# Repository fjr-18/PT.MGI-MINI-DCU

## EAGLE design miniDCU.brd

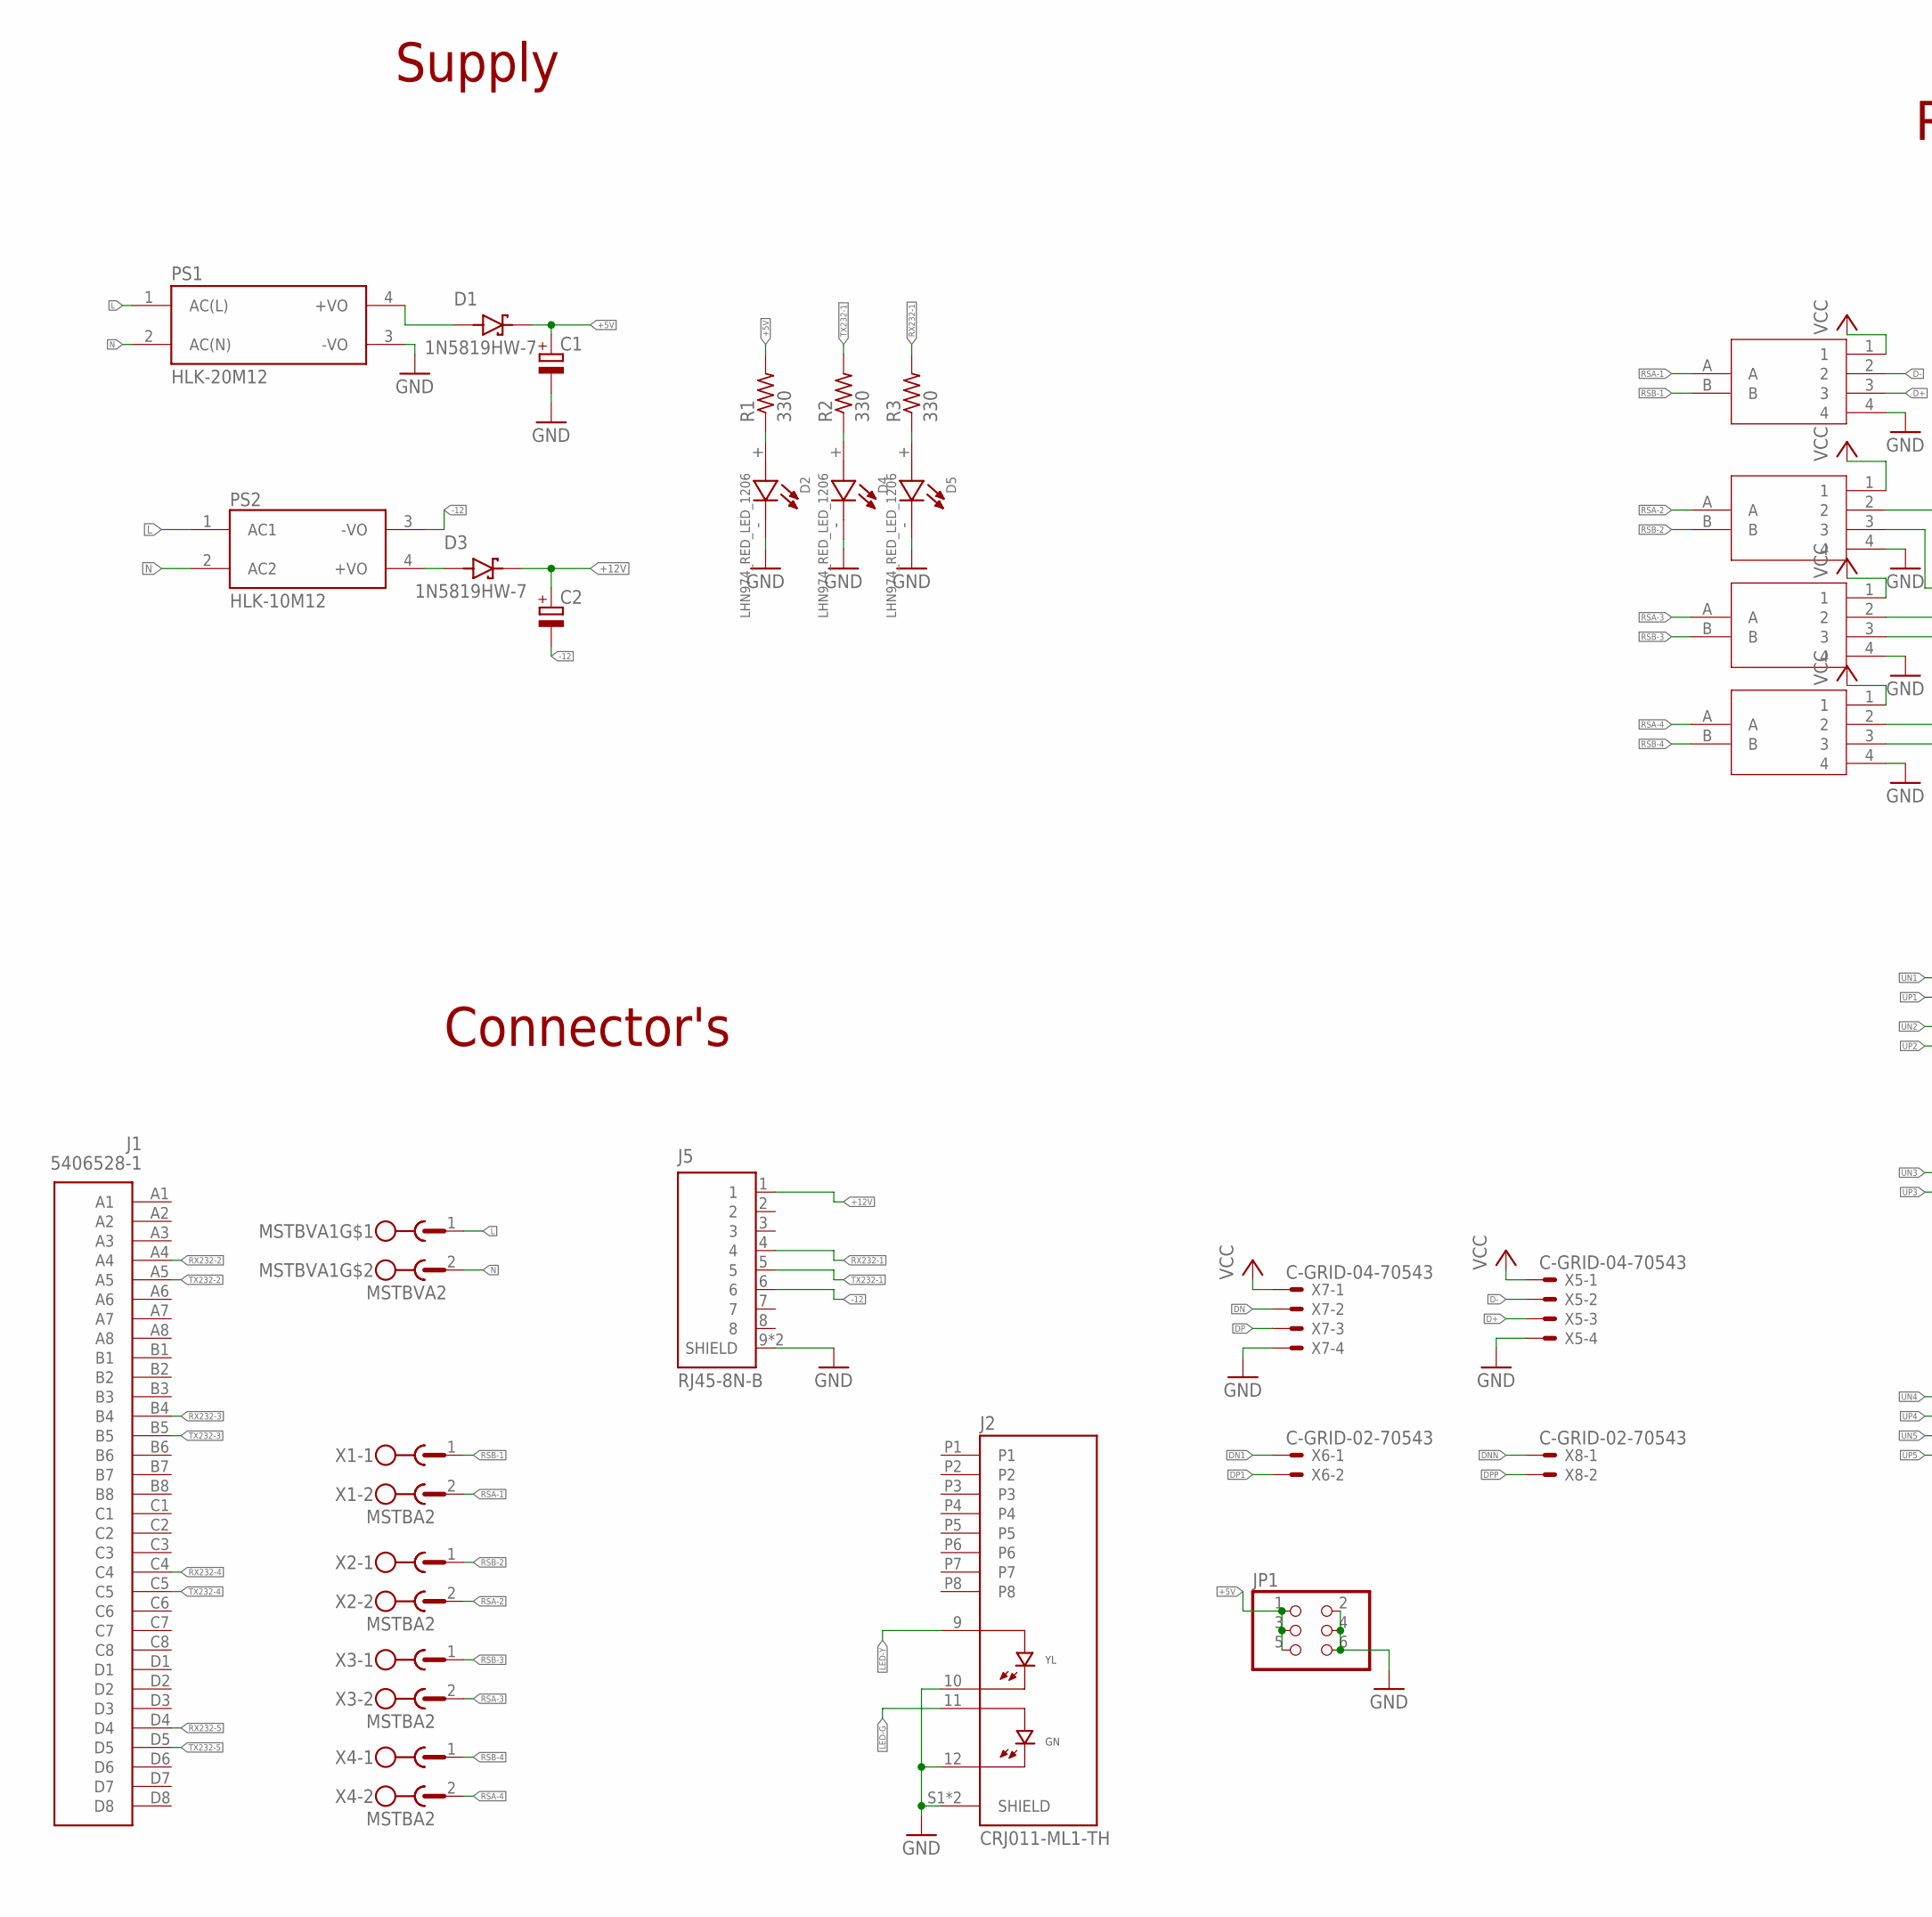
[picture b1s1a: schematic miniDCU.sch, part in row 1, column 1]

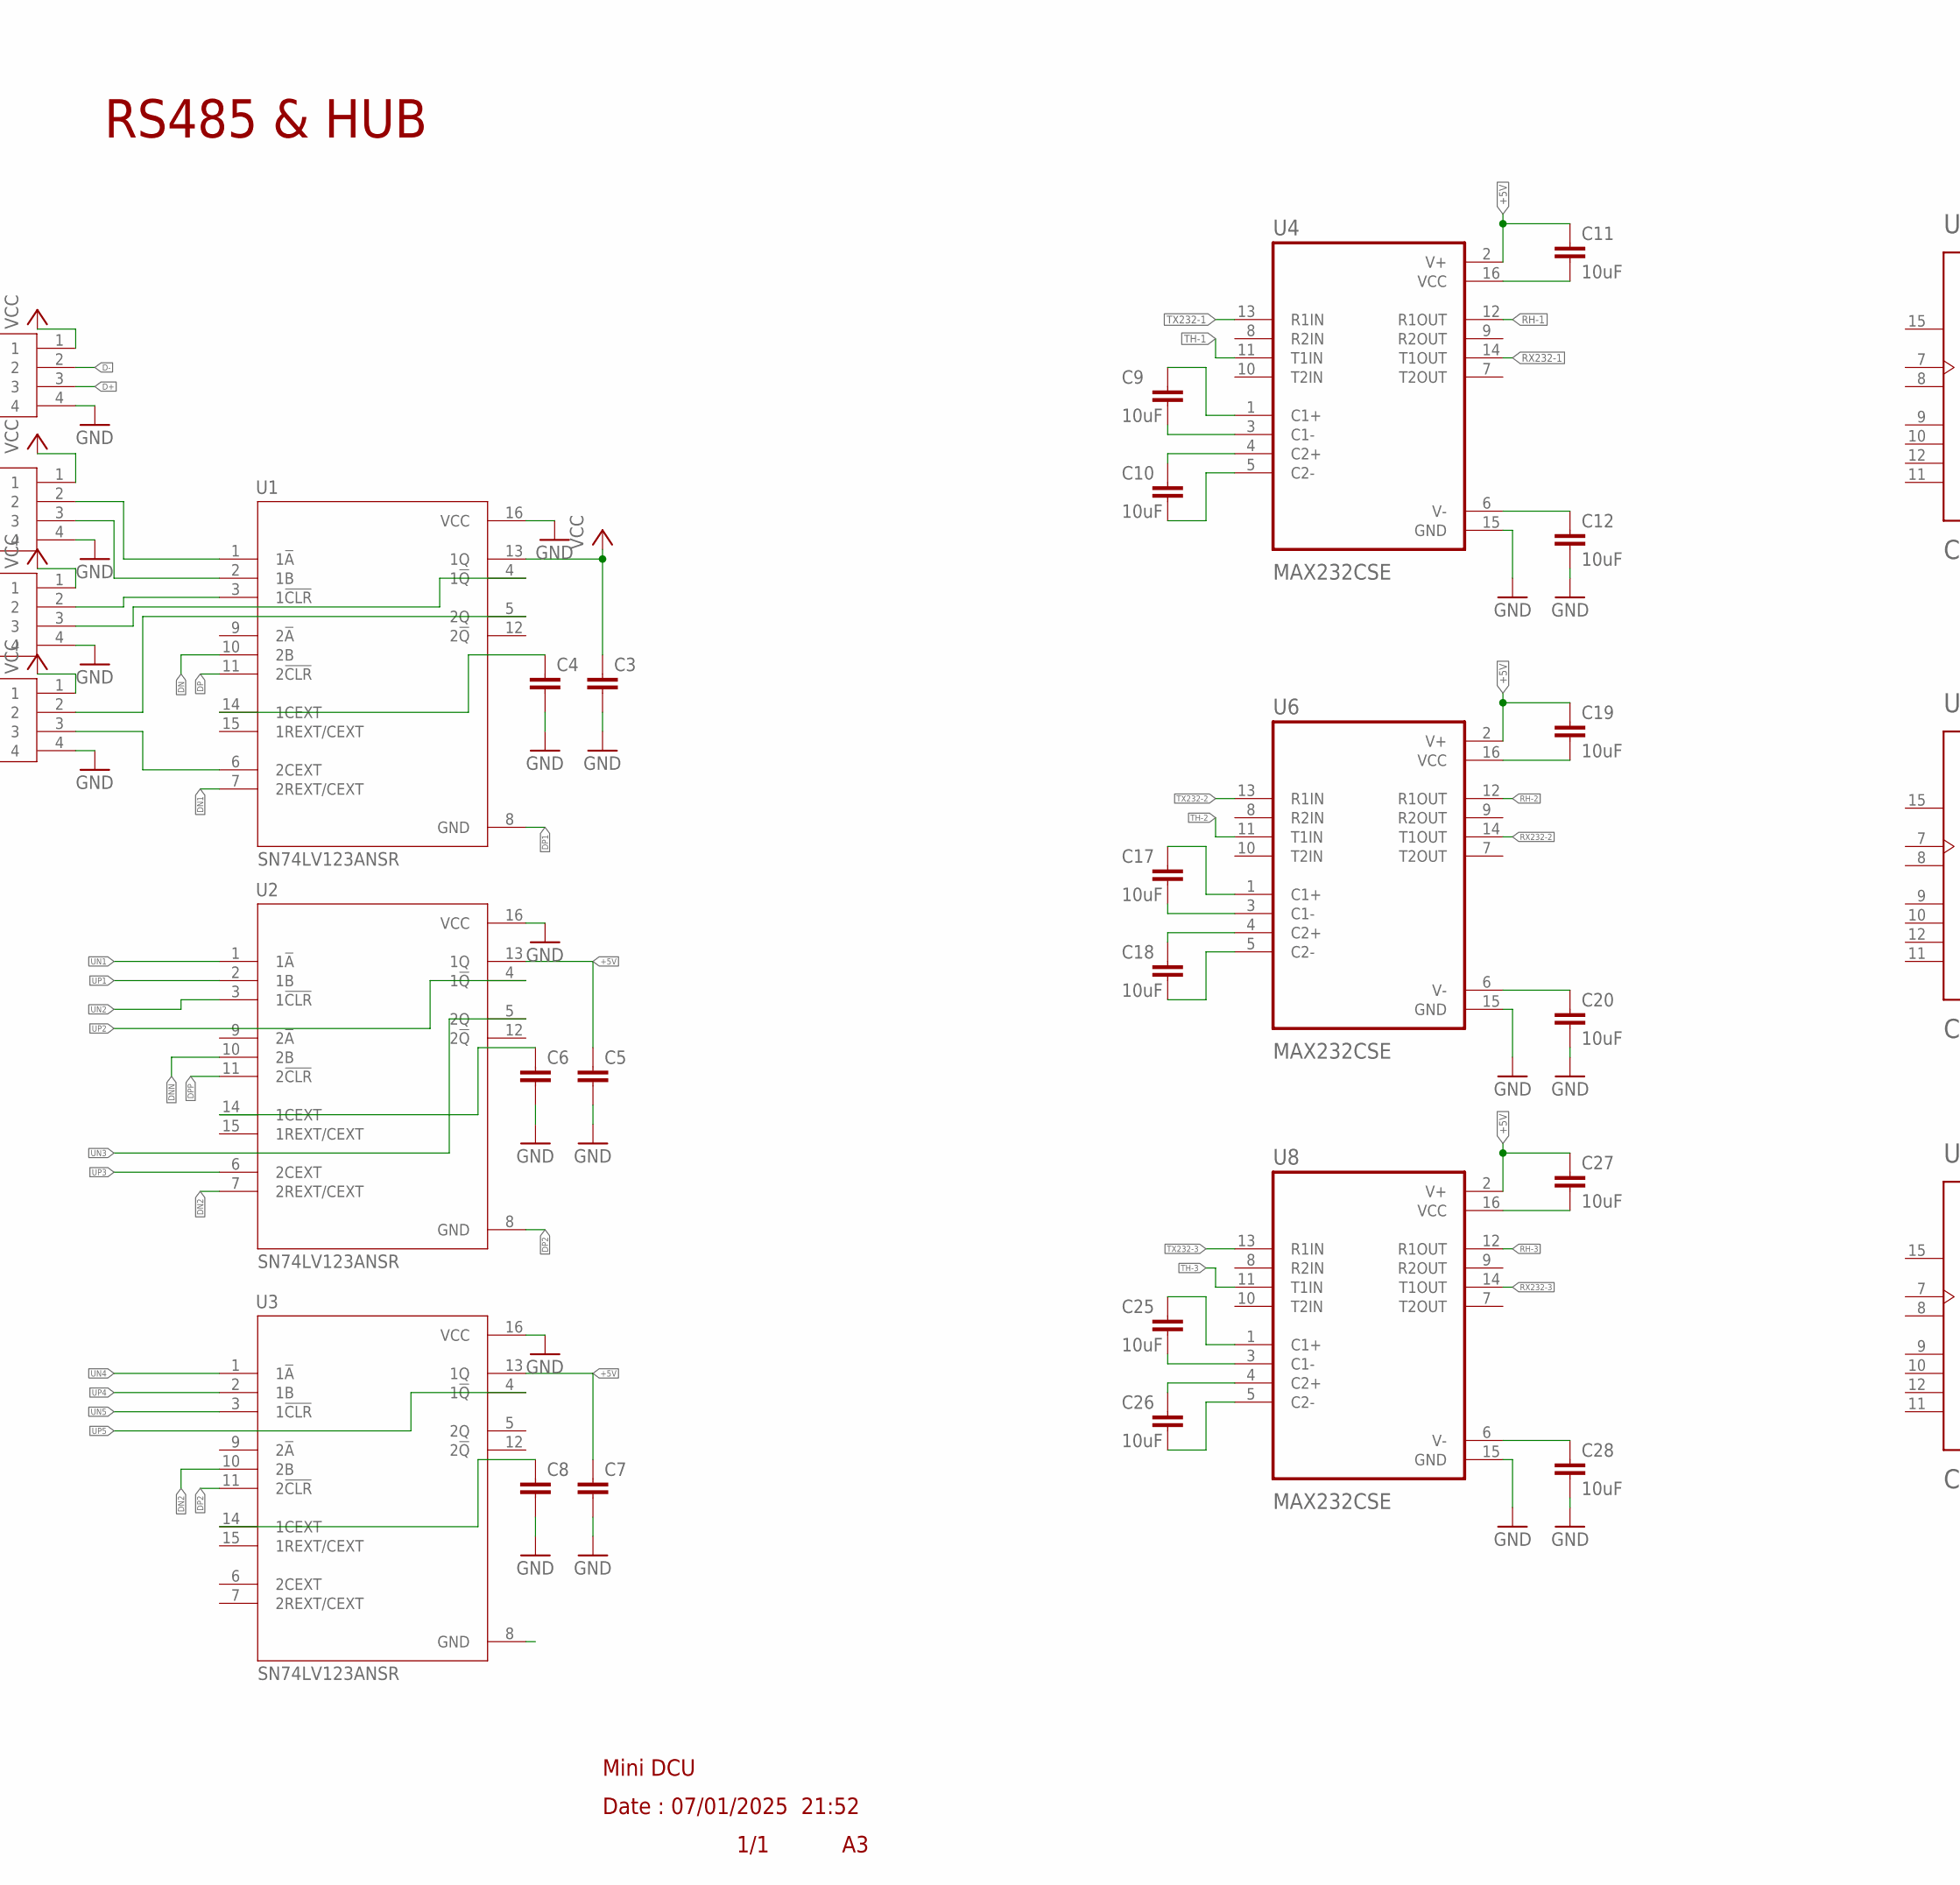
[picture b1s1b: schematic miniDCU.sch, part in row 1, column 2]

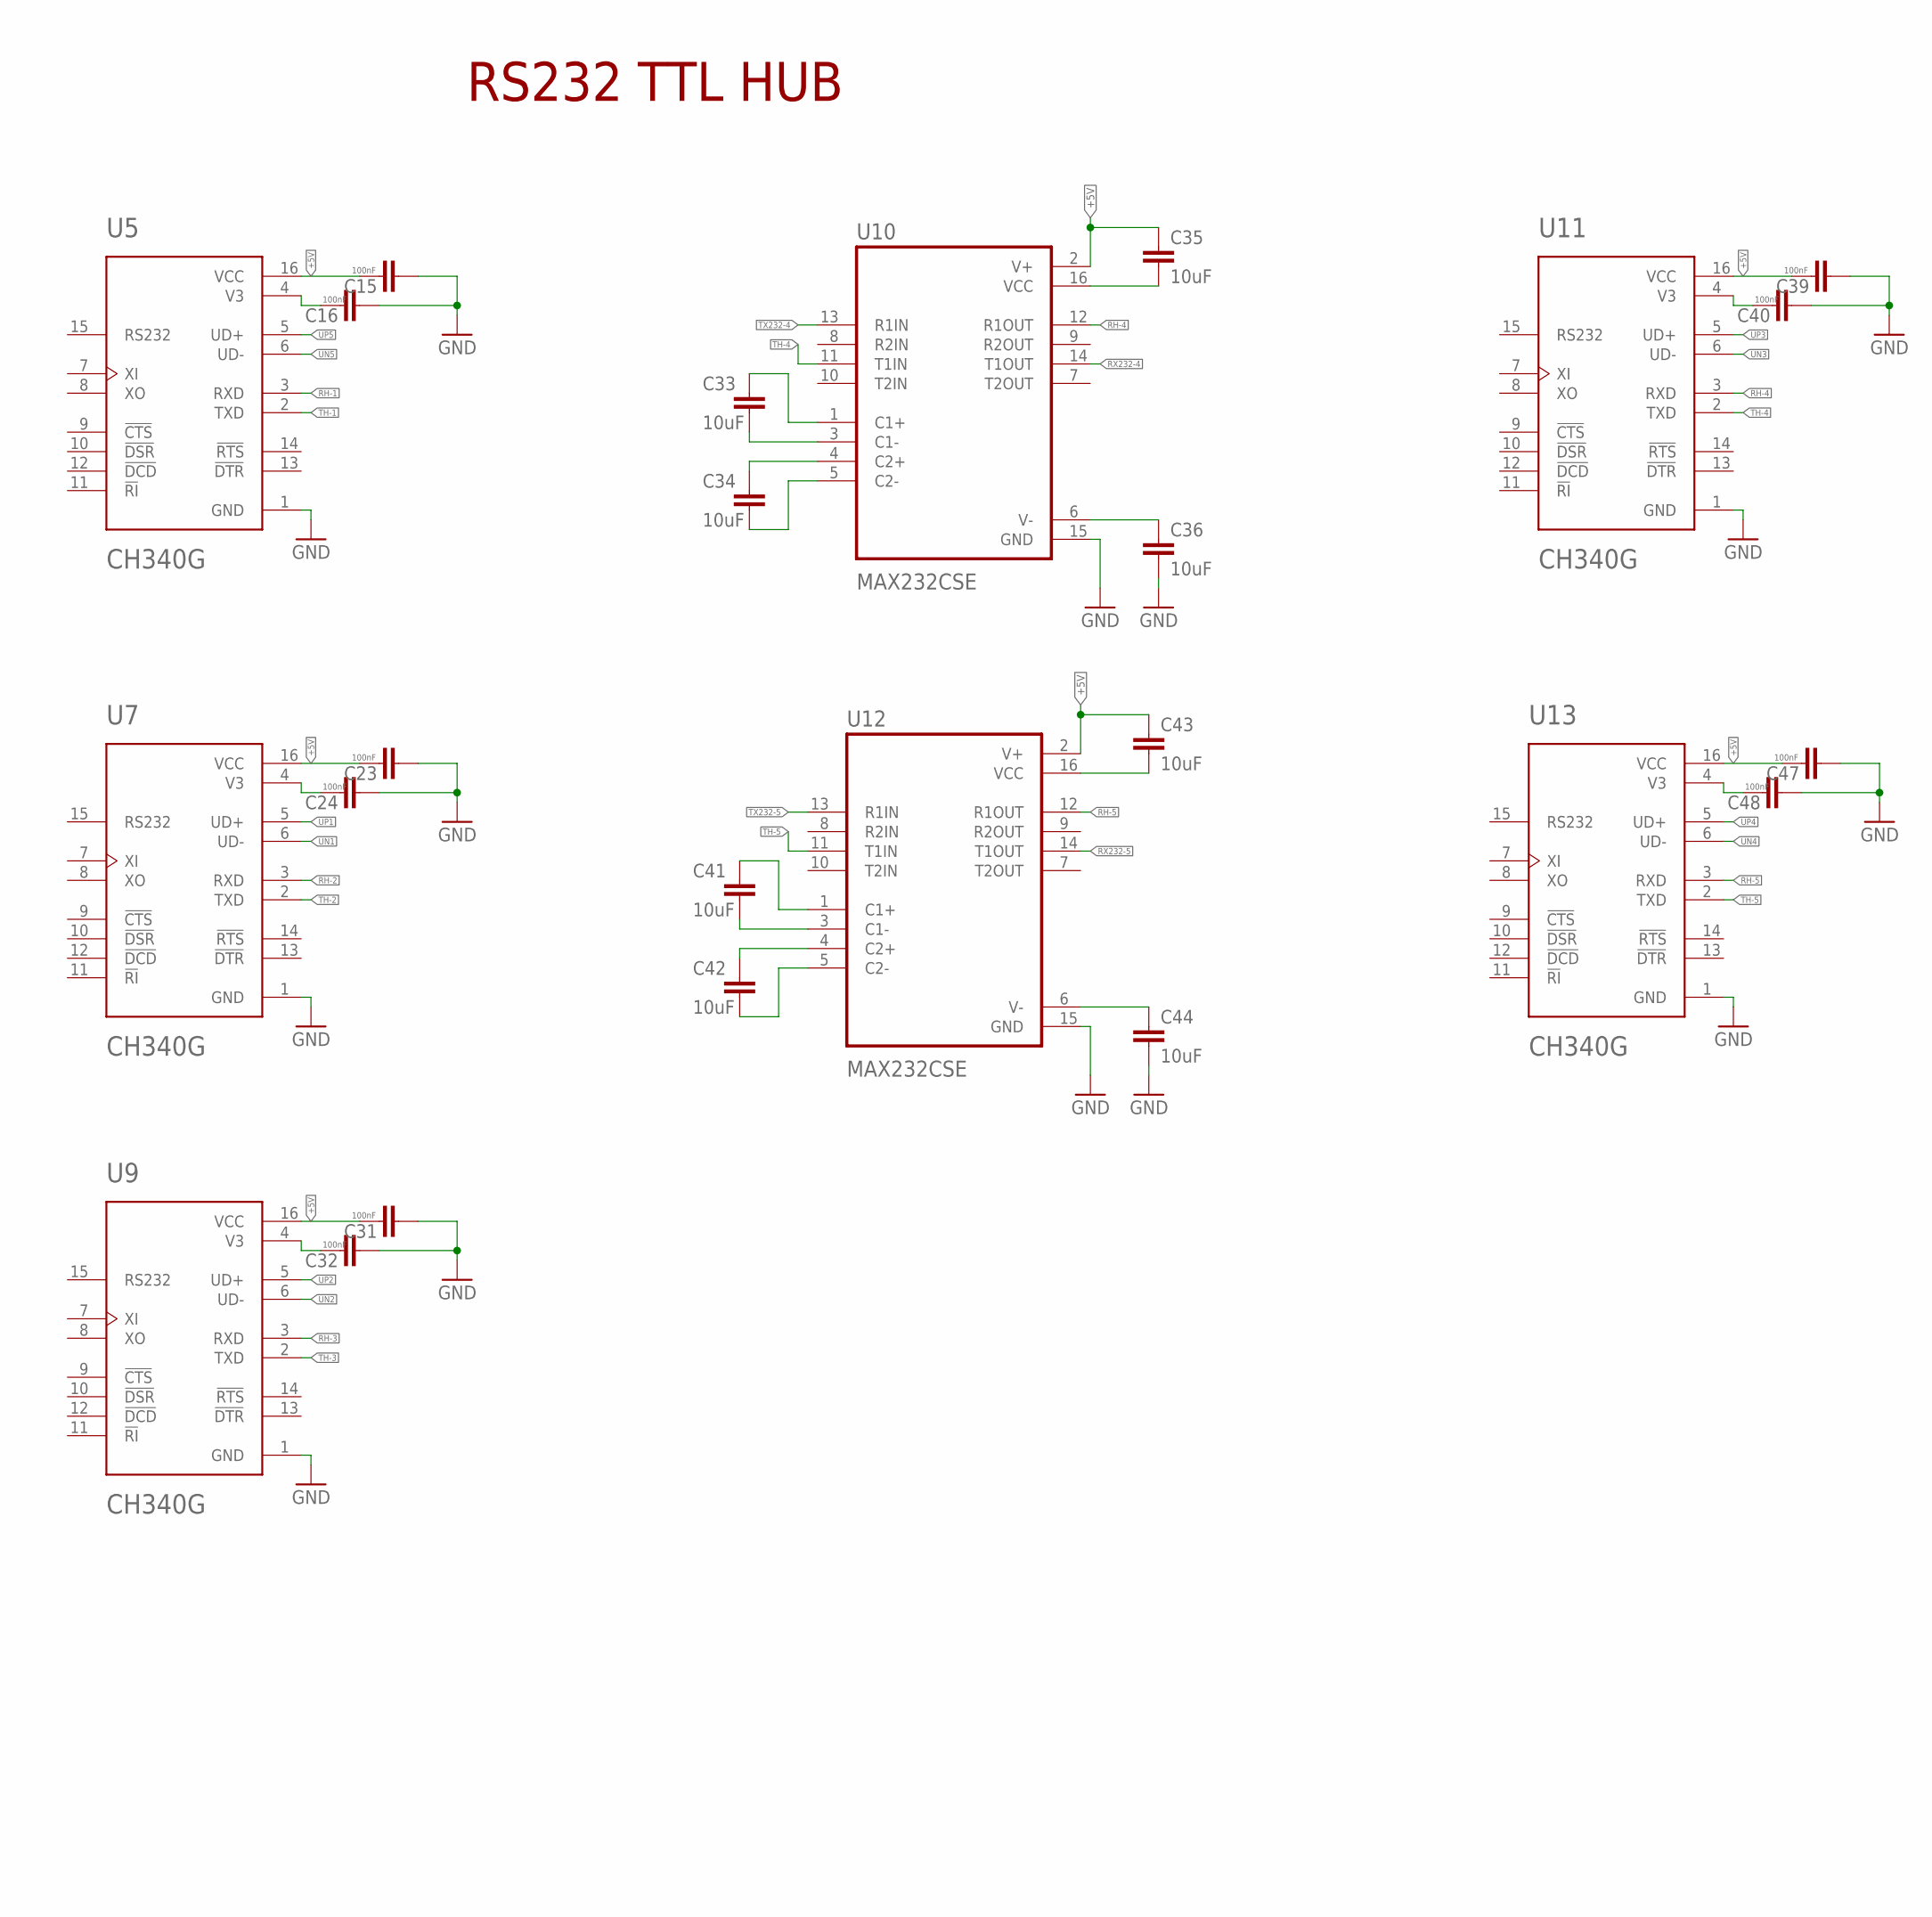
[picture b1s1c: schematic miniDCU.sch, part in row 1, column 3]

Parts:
C1, C2: CPOL-EU153CLV-0505; 153CLV-0505
C3, C4, C5, C6, C7, C8: C-EUC0603K; C0603K
C9, C10, C11, C12, C17, C18, C19, C20, C25, C26, C27, C28, C33, C34, C35, C36, C41, C42, C43, C44: 10uF; C0805
C15, C16, C23, C24, C31, C32, C39, C40, C47, C48: 100nF; C0805K
D1, D3: 1N5819HW-7; SOD3715X145N
D2, D4, D5: LHN974_RED_LED_1206; LEDC3216X120N
J1: 5406528-1
J2: CRJ011-ML1-TH; CUI_CRJ011-ML1-TH
J5: RJ45-8N-B; TE_RJ45-8N-B
JP1: PINHD-2X3; 2X03
MSTBVA1: MSTBVA2
PS1: HLK-20M12; CONV_HLK-20M12
PS2: HLK-10M12; CONV_HLK-10M12
R1, R2, R3: 330; M0805
U1, U2, U3: SN74LV123ANSR; SOIC127P780X200-16N
U4, U6, U8, U10, U12: MAX232CSE; SOIC127P600X175-16N
U5, U7, U9, U11, U13: CH340G; SOIC127P600X180-16N
USB2RS1, USB2RS2, USB2RS3, USB2RS5: USB2RS485
X1, X2, X3, X4: MSTBA2
X5, X7: C-GRID-04-70543; 70543-04
X6, X8: C-GRID-02-70543; 70543-02

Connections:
+5V: C1.+, C5.1, C7.1, C11.1, C15.1, C19.1, C23.1, C27.1, C31.1, C35.1, C39.1, C43.1, C47.1, D1.C (K), JP1.1, JP1.3, JP1.5, R1.2, U2.13 (1Q), U3.13 (1Q), U4.2 (V+), U5.16 (VCC), U6.2 (V+), U7.16 (VCC), U8.2 (V+), U9.16 (VCC), U10.2 (V+), U11.16 (VCC), U12.2 (V+), U13.16 (VCC)
+12V: C2.+, D3.C (K), J5.1
-12: C2.-, J5.6, PS2.3 (-VO)
D+: USB2RS5.3, X5.3
D-: USB2RS5.2, X5.2
DN: U1.10 (2B), X7.2
DN1: U1.7 (2REXT/CEXT), X6.1
DN2: U2.7 (2REXT/CEXT), U3.10 (2B)
DNN: U2.10 (2B), X8.1
DP: U1.11 (2!CLR), X7.3
DP1: U1.8 (GND), X6.2
DP2: U2.8 (GND), U3.11 (2!CLR)
DPP: U2.11 (2!CLR), X8.2
GND: C1.-, C3.2, C4.2, C5.2, C6.2, C7.2, C8.2, C12.2, C15.2, C16.2, C20.2, C23.2, C24.2, C28.2, C31.2, C32.2, C36.2, C39.2, C40.2, C44.2, C47.2, C48.2, D2.-, D4.-, D5.-, J2.10, J2.12, J2.S1 (SHIELD), J2.S2 (SHIELD), J5.9 (SHIELD), J5.10 (SHIELD), JP1.2, JP1.4, JP1.6, PS1.3 (-VO), U1.16 (VCC), U2.16 (VCC), U3.16 (VCC), U4.15 (GND), U5.1 (GND), U6.15 (GND), U7.1 (GND), U8.15 (GND), U9.1 (GND), U10.15 (GND), U11.1 (GND), U12.15 (GND), U13.1 (GND), USB2RS1.4, USB2RS2.4, USB2RS3.4, USB2RS5.4, X5.4, X7.4
L: MSTBVA1.1, PS1.1 (AC(L)), PS2.1 (AC1)
LED-G: J2.11
LED-Y: J2.9
N: MSTBVA1.2, PS1.2 (AC(N)), PS2.2 (AC2)
unnamed: D1.A, PS1.4 (+VO)
unnamed: D4.+, R2.1
unnamed: D2.+, R1.1
unnamed: D5.+, R3.1
unnamed: D3.A, PS2.4 (+VO)
unnamed: C9.2, U4.3 (C1-)
unnamed: C9.1, U4.1 (C1+)
unnamed: C10.1, U4.4 (C2+)
unnamed: C10.2, U4.5 (C2-)
unnamed: C11.2, U4.16 (VCC)
unnamed: C12.1, U4.6 (V-)
unnamed: U1.1 (1!A), USB2RS1.2
unnamed: U1.2 (1B), USB2RS1.3
unnamed: U1.3 (1!CLR), USB2RS2.2
unnamed: U1.4 (1!Q), USB2RS2.3
unnamed: U1.5 (2Q), USB2RS3.2
unnamed: U1.6 (2CEXT), USB2RS3.3
unnamed: C16.1, U5.4 (V3)
unnamed: C17.2, U6.3 (C1-)
unnamed: C17.1, U6.1 (C1+)
unnamed: C18.1, U6.4 (C2+)
unnamed: C18.2, U6.5 (C2-)
unnamed: C19.2, U6.16 (VCC)
unnamed: C20.1, U6.6 (V-)
unnamed: C24.1, U7.4 (V3)
unnamed: C25.2, U8.3 (C1-)
unnamed: C25.1, U8.1 (C1+)
unnamed: C26.1, U8.4 (C2+)
unnamed: C26.2, U8.5 (C2-)
unnamed: C27.2, U8.16 (VCC)
unnamed: C28.1, U8.6 (V-)
unnamed: C32.1, U9.4 (V3)
unnamed: C33.2, U10.3 (C1-)
unnamed: C33.1, U10.1 (C1+)
unnamed: C34.1, U10.4 (C2+)
unnamed: C4.1, U1.14 (1CEXT)
unnamed: C8.1, U3.14 (1CEXT)
unnamed: C34.2, U10.5 (C2-)
unnamed: C35.2, U10.16 (VCC)
unnamed: C36.1, U10.6 (V-)
unnamed: C6.1, U2.14 (1CEXT)
unnamed: C40.1, U11.4 (V3)
unnamed: C41.2, U12.3 (C1-)
unnamed: C41.1, U12.1 (C1+)
unnamed: C42.1, U12.4 (C2+)
unnamed: C42.2, U12.5 (C2-)
unnamed: C43.2, U12.16 (VCC)
unnamed: C44.1, U12.6 (V-)
unnamed: C48.1, U13.4 (V3)
RH-1: U4.12 (R1OUT), U5.3 (RXD)
RH-2: U6.12 (R1OUT), U7.3 (RXD)
RH-3: U8.12 (R1OUT), U9.3 (RXD)
RH-4: U10.12 (R1OUT), U11.3 (RXD)
RH-5: U12.12 (R1OUT), U13.3 (RXD)
RSA-1: USB2RS5.A, X1.2
RSA-2: USB2RS1.A, X2.2
RSA-3: USB2RS2.A, X3.2
RSA-4: USB2RS3.A, X4.2
RSB-1: USB2RS5.B, X1.1
RSB-2: USB2RS1.B, X2.1
RSB-3: USB2RS2.B, X3.1
RSB-4: USB2RS3.B, X4.1
RX232-1: J5.4, R3.2, U4.14 (T1OUT)
RX232-2: J1.A4, U6.14 (T1OUT)
RX232-3: J1.B4, U8.14 (T1OUT)
RX232-4: J1.C4, U10.14 (T1OUT)
RX232-5: J1.D4, U12.14 (T1OUT)
TH-1: U4.11 (T1IN), U5.2 (TXD)
TH-2: U6.11 (T1IN), U7.2 (TXD)
TH-3: U8.11 (T1IN), U9.2 (TXD)
TH-4: U10.11 (T1IN), U11.2 (TXD)
TH-5: U12.11 (T1IN), U13.2 (TXD)
TX232-1: J5.5, R2.2, U4.13 (R1IN)
TX232-2: J1.A5, U6.13 (R1IN)
TX232-3: J1.B5, U8.13 (R1IN)
TX232-4: J1.C5, U10.13 (R1IN)
TX232-5: J1.D5, U12.13 (R1IN)
UN1: U2.1 (1!A), U7.6 (UD-)
UN2: U2.3 (1!CLR), U9.6 (UD-)
UN3: U2.5 (2Q), U11.6 (UD-)
UN4: U3.1 (1!A), U13.6 (UD-)
UN5: U3.3 (1!CLR), U5.6 (UD-)
UP1: U2.2 (1B), U7.5 (UD+)
UP2: U2.4 (1!Q), U9.5 (UD+)
UP3: U2.6 (2CEXT), U11.5 (UD+)
UP4: U3.2 (1B), U13.5 (UD+)
UP5: U3.4 (1!Q), U5.5 (UD+)
VCC: C3.1, U1.13 (1Q), USB2RS1.1, USB2RS2.1, USB2RS3.1, USB2RS5.1, X5.1, X7.1

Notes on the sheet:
Mini DCU
Date : 07/01/2025 21:52
1/1
Supply
Connector's
RS485 & HUB
RS232 TTL HUB

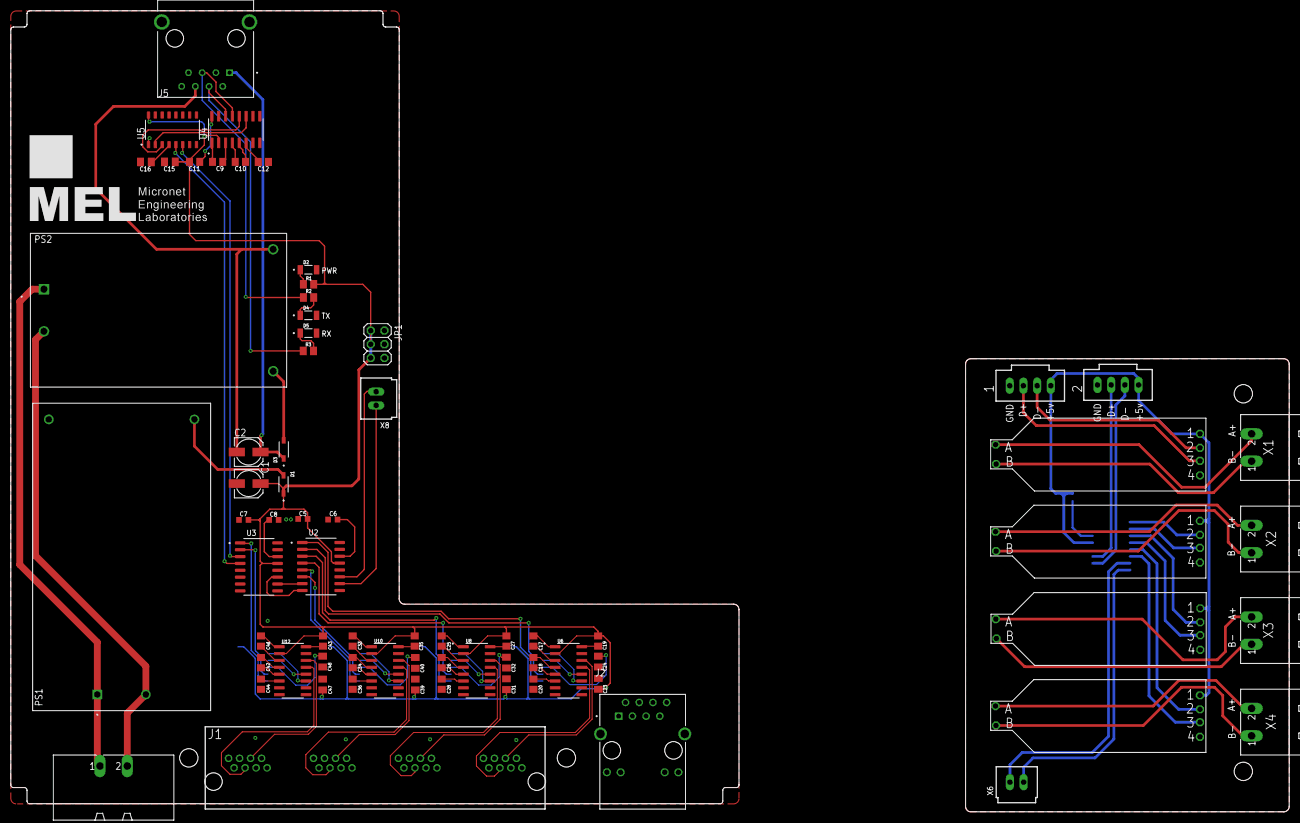
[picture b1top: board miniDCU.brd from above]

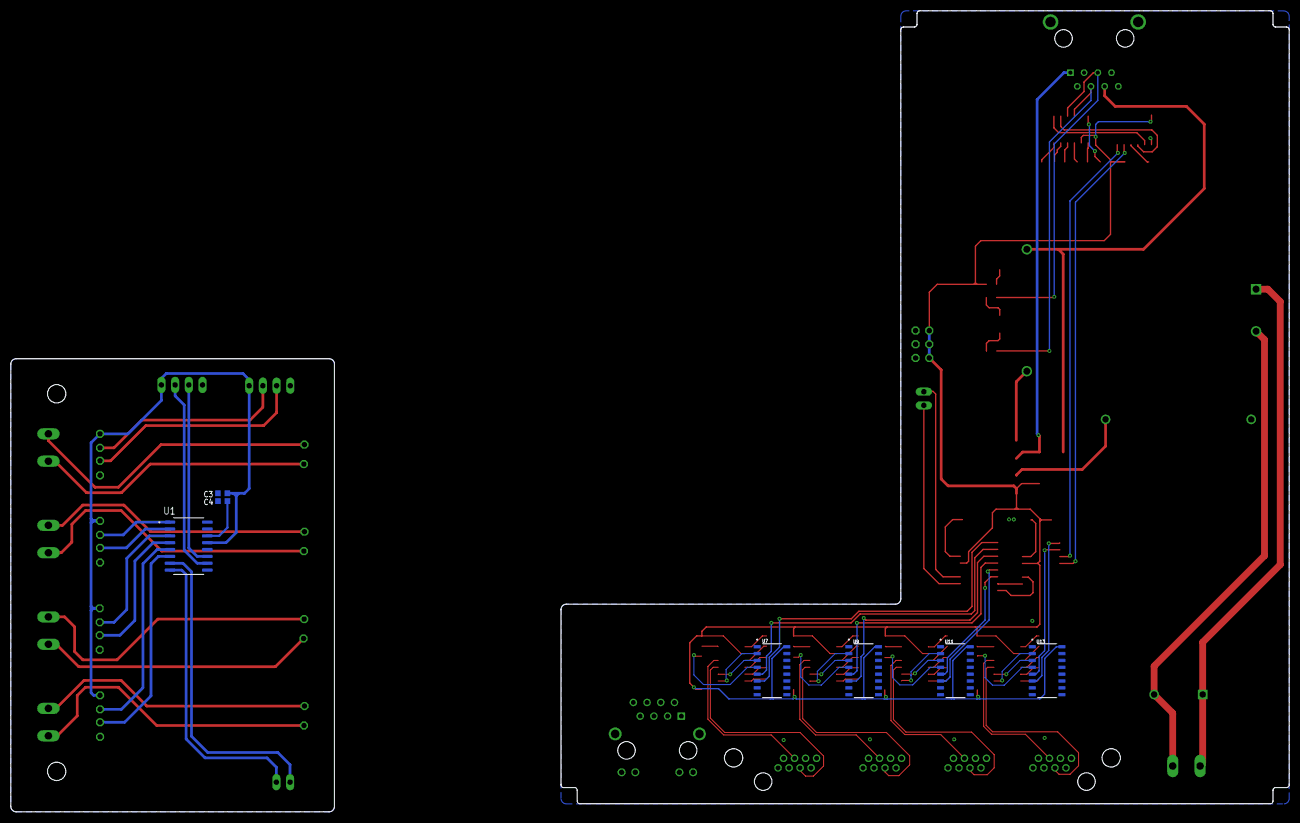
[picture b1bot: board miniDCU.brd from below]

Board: 2 copper layers, 237.0 x 148.5 mm, 78 parts (7 on the bottom side), 104 nets.

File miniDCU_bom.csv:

Comment,Designator,Footprint,LCSC Part #
,JP1,2X03,
,C1,153CLV-0505,
,C2,153CLV-0505,
,C3,C0603K,
,C4,C0603K,
,C5,C0603K,
,C6,C0603K,
,C7,C0603K,
,C8,C0603K,
,USB2RS1,USB2RS485,
,USB2RS2,USB2RS485,
,USB2RS3,USB2RS485,
,USB2RS5,USB2RS485,
1N5819HW-7,D1 D3,SOD3715X145N,
10uF,C9 C10 C11 C12 C17 C18 C19 C20 C25 C26 C27 C28 C33 C34 C35 C36 C41 C42 C43 C44,C0805,
100nF,C15 C16 C23 C24 C31 C32 C39 C40 C47 C48,C0805K,
330,R1,M0805,
5406528-1,J1,5406528-1,
C-GRID-02-70543,X6 X8,70543-02,
C-GRID-04-70543,X5 X7,70543-04,
CH340G,U5 U7 U9 U11 U13,SOIC127P600X180-16N,
CRJ011-ML1-TH,J2,CUI_CRJ011-ML1-TH,
HLK-10M12,PS2,CONV_HLK-10M12,
HLK-20M12,PS1,CONV_HLK-20M12,
LHN974_RED_LED_1206,D2,LEDC3216X120N,
MAX232CSE,U4 U6 U8 U10 U12,SOIC127P600X175-16N,
MSTBA2,X1 X2 X3 X4,MSTBA2,
MSTBVA2,MSTBVA1,MSTBVA2,
RJ45-8N-B,J3 J5,TE_RJ45-8N-B,
SN74LV123ANSR,U1 U2 U3,SOIC127P780X200-16N,
